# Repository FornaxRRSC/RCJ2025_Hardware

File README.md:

# Hardware

機体に搭載している基板のリポジトリです。  
それぞれの基板の解説は<https://fornax-rrsc.com>に掲載しています。

## 既知の欠陥

最新の基板の欠陥のみ記載
* MainBoard Rev.3のSTM32H723とSTM32F446間のUARTがTX,RX同士をつないでいる
* MainBoard Rev.3のオペアンプのフットプリントが間違っている

## License

**CERN-OHL-P v2**

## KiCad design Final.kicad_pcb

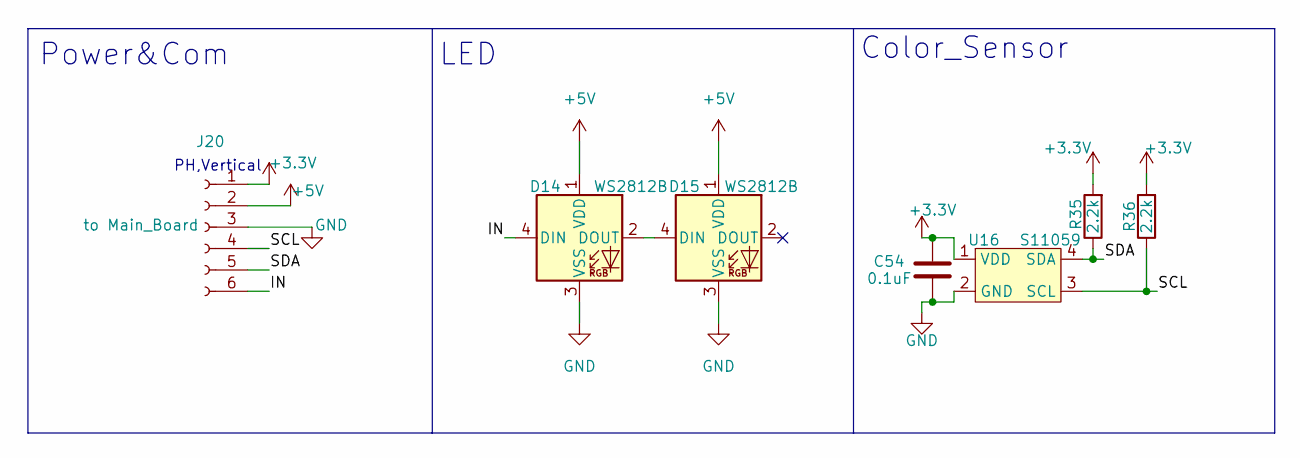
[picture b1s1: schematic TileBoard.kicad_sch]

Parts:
C54: 0.1uF; C_0603_1608Metric
D14, D15: WS2812B; LED_WS2812B_PLCC4_5.0x5.0mm_P3.2mm
J20: to Main_Board; PinHeader_1x06_P2.54mm_Vertical
R35, R36: 2.2k; R_0603_1608Metric
U16: S11059

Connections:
+3.3V: C54.1, J20.1, R35.2, R36.2, U16.1 (VDD); also elsewhere on the board
+5V: D14.1 (VDD), D15.1 (VDD), J20.2; also elsewhere on the board
/Tile_Board/IN: D14.4 (DIN), J20.6
/Tile_Board/SCL: J20.4, R36.1, U16.3 (SCL)
/Tile_Board/SDA: J20.5, R35.1, U16.4 (SDA)
GND: C54.2, D14.3 (VSS), D15.3 (VSS), J20.3, U16.2 (GND); also elsewhere on the board
unnamed: D14.2 (DOUT), D15.4 (DIN)

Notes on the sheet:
Color_Sensor
LED
Power&Com
PH,Vertical

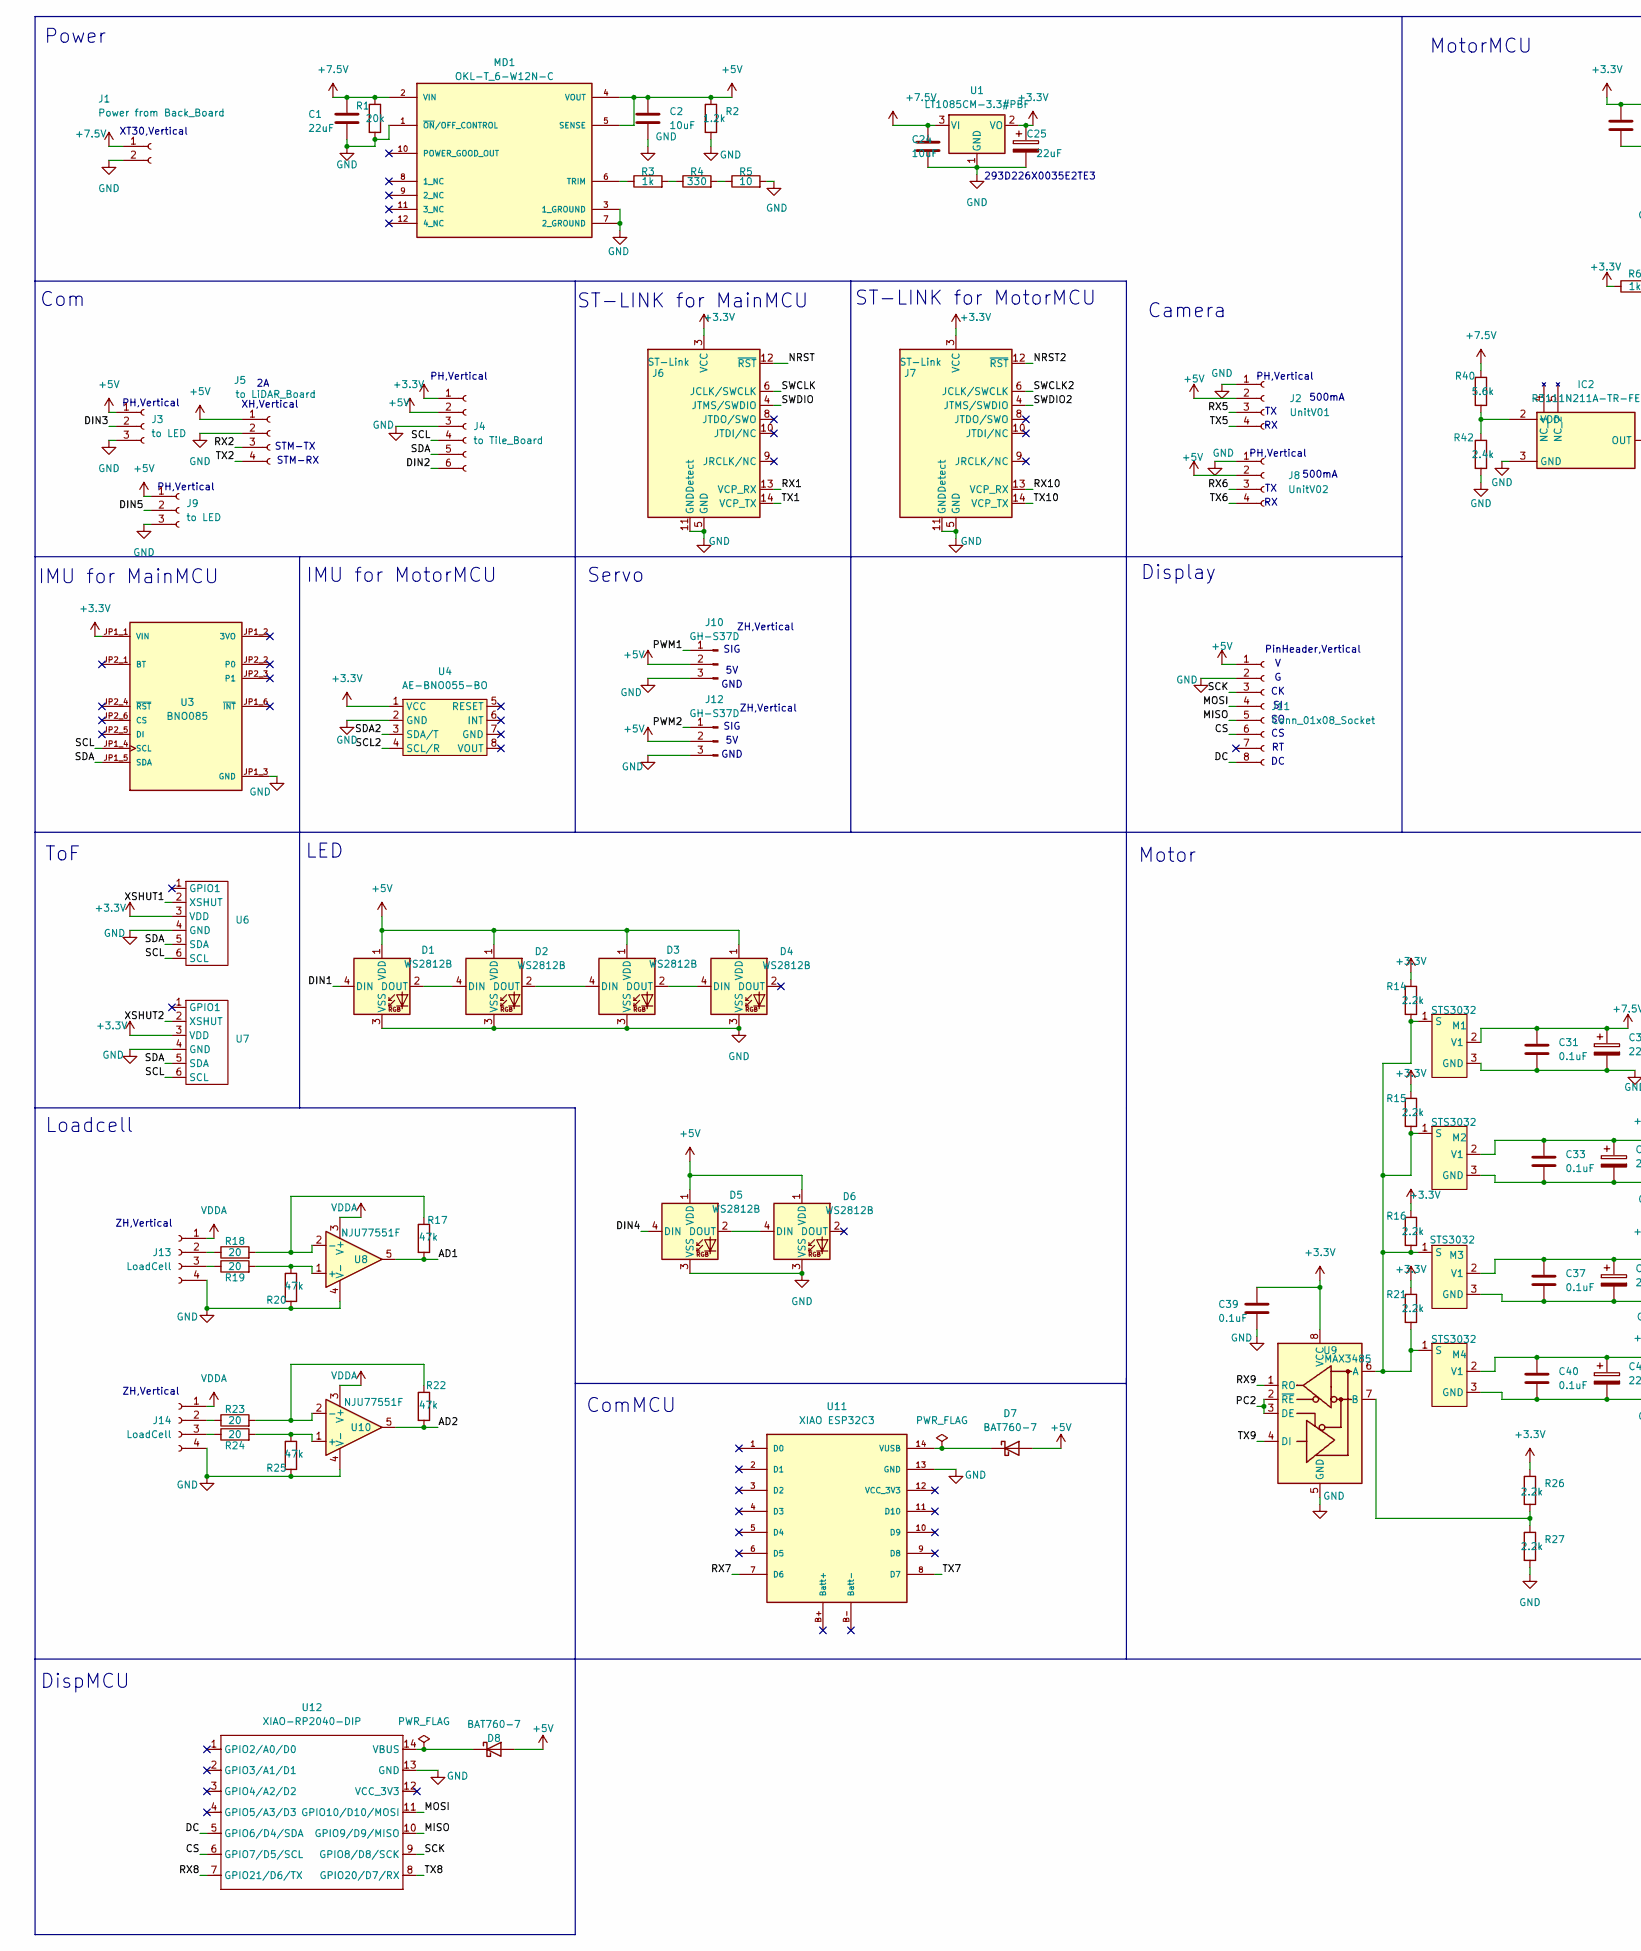
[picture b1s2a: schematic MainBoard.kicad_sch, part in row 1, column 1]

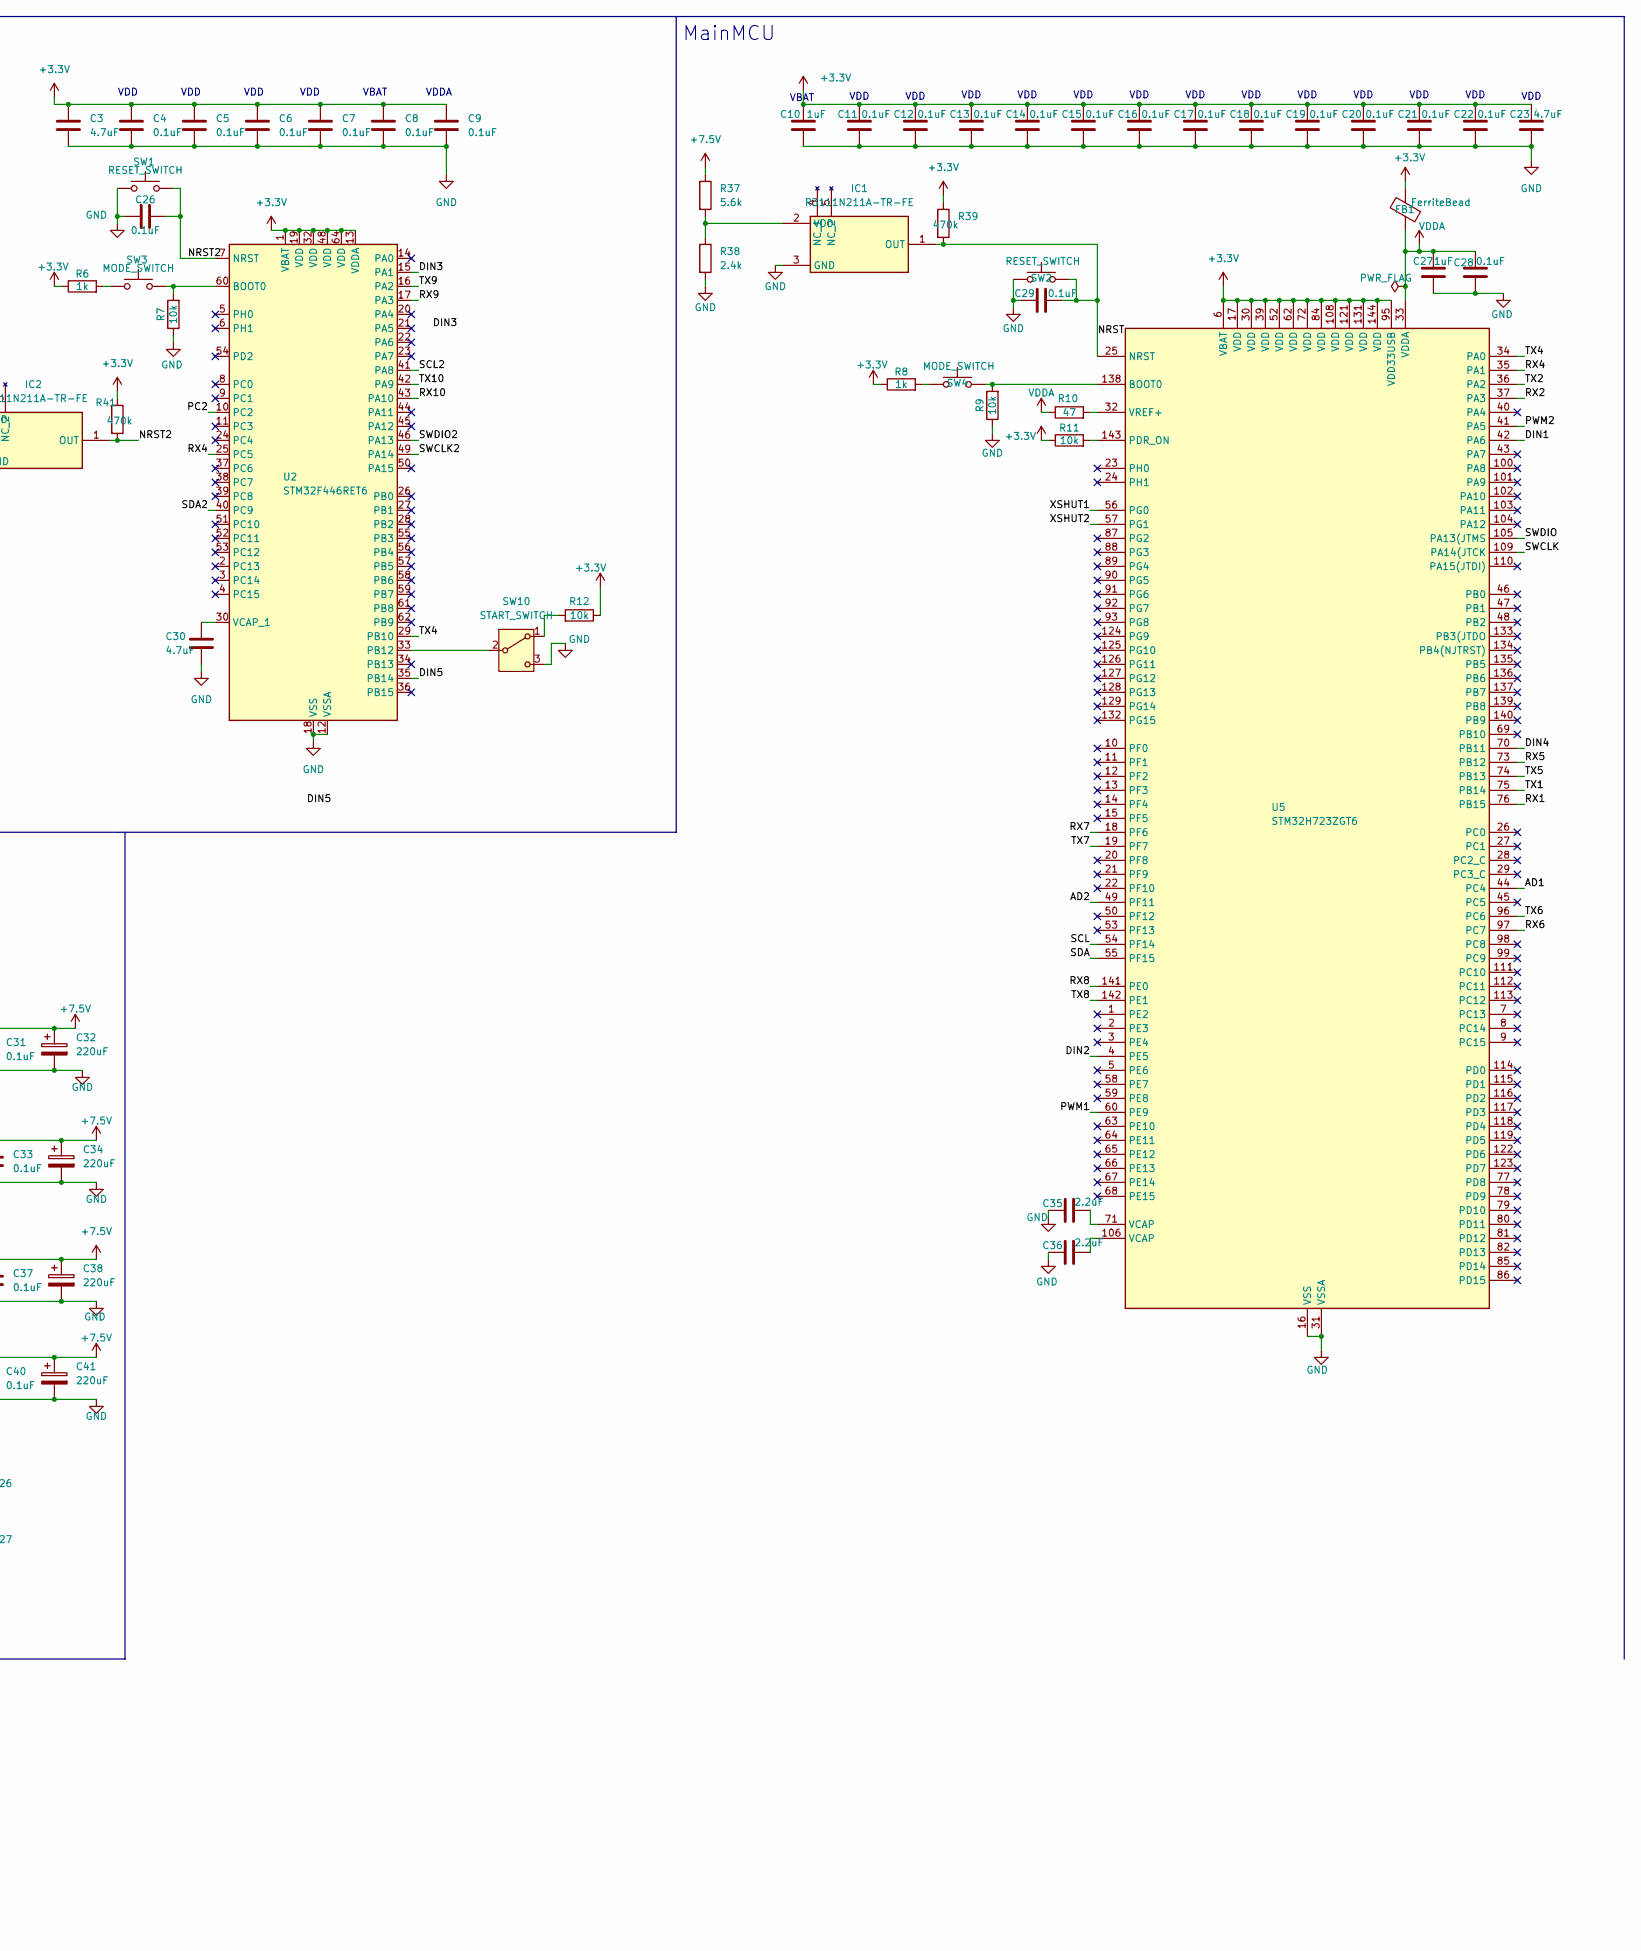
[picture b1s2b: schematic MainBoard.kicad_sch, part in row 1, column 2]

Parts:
C1: 22uF; C_0402_1005Metric
C2: 10uF; C_0402_1005Metric
C3, C23, C30: 4.7uF; C_0402_1005Metric
C4, C5, C6, C7, C8, C9, C11, C12, C13, C14, C15, C16, C17, C18, C19, C20, C21, C22, C28, C31, C33, C37, C39, C40: 0.1uF; C_0402_1005Metric
C10, C27: 1uF; C_0402_1005Metric
C24: 10uF; C_0603_1608Metric_Pad1.08x0.95mm_HandSolder
C25: 22uF; CP_EIA-7343-15_Kemet-W
C26, C29: 0.1uF; C_0603_1608Metric_Pad1.08x0.95mm_HandSolder
C32, C34, C38, C41: 220uF; CP_Elec_10x10
C35, C36: 2.2uF; C_0402_1005Metric
D1, D2, D3, D4, D5, D6: WS2812B; LED_WS2812B_PLCC4_5.0x5.0mm_P3.2mm
D7, D8: BAT760-7; D_SOD-323F
FB1: FerriteBead; L_0603_1608Metric
IC1, IC2: R3111N211A-TR-FE; SOT95P280X130-5N; Mouser Part Number 848-R3111N211A-TR-FE
J1: Power from Back_Board; AMASS_XT30U-M_1x02_P5.0mm_Vertical
J2: UnitV01; JST_PH_B4B-PH-K_1x04_P2.00mm_Vertical
J3, J9: to LED; JST_PH_B3B-PH-K_1x03_P2.00mm_Vertical
J4: to Tile_Board; PinSocket_1x06_P2.54mm_Vertical
J5: to LiDAR_Board; JST_XH_B4B-XH-A_1x04_P2.50mm_Vertical
J6, J7: ST-Link; CONN14_3220-14_CNC
J8: UnitV02; JST_PH_B4B-PH-K_1x04_P2.00mm_Vertical
J10, J12: GH-S37D; JST_ZH_B3B-ZR_1x03_P1.50mm_Vertical
J11: Conn_01x08_Socket; PinSocket_1x08_P2.54mm_Vertical
J13, J14: LoadCell; JST_ZH_B4B-ZR_1x04_P1.50mm_Vertical
M1, M2, M3, M4: STS3032; JST_XH_B3B-XH-A_1x03_P2.50mm_Vertical
MD1: OKL-T_6-W12N-C; MURATA_OKL-T-6-W12N-C_0; MOUSER_PART_NUMBER 580-OKL-T/6-W12N-C; MOUSER_DESCRIPTION Non-Isolated DC/DC Converters 12Vin .59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
R1: 20k; R_0402_1005Metric
R2: 1.2k; R_0402_1005Metric
R3: 1k; R_0402_1005Metric
R4: 330; R_0402_1005Metric
R5: 10; R_0402_1005Metric
R6, R8: 1k; R_0603_1608Metric_Pad0.98x0.95mm_HandSolder
R7, R9: 10k; R_0603_1608Metric_Pad0.98x0.95mm_HandSolder
R10: 47; R_0402_1005Metric
R11, R12: 10k; R_0402_1005Metric
R14, R15, R16, R21, R26, R27: 2.2k; R_0402_1005Metric
R17, R20, R22, R25: 47k; R_0402_1005Metric
R18, R19, R23, R24: 20; R_0402_1005Metric
R37, R40: 5.6k; R_0402_1005Metric
R38, R42: 2.4k; R_0402_1005Metric
R39, R41: 470k; R_0402_1005Metric
SW1, SW2: RESET_SWITCH; SW_SKRPACE010
SW3, SW4: MODE_SWITCH; SW_SKRPACE010
SW10: START_SWITCH; B12AP_NKK
U1: LT1085CM-3.3#PBF; TO-263-3_TabPin2
U2: STM32F446RET6; LQFP-64_10x10mm_P0.5mm
U3: BNO085; PARTREV 2021-03-16
U4: AE-BNO055-BO
U5: STM32H723ZGT6; LQFP-144_20x20mm_P0.5mm
U6, U7: PinSocket_1x06_P2.54mm_Vertical
U8, U10: NJU77551F; SOT-23-5
U9: MAX3485; SOIC-8_3.9x4.9mm_P1.27mm
U11: XIAO ESP32C3; XIAO-14P-DIP
U12: XIAO-RP2040-DIP; XIAO-14P-DIP

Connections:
+3.3V: C3.1, C4.1, C5.1, C6.1, C7.1, C8.1, C9.1, C10.1, C11.1, C12.1, C13.1, C14.1, C15.1, C16.1, C17.1, C18.1, C19.1, C20.1, C21.1, C22.1, C23.1, C25.1, C39.1, FB1.2, J4.1, J6.3 (VCC), J7.3 (VCC), R6.1, R8.1, R11.1, R12.1, R14.1, R15.1, R16.1, R21.1, R26.1, R39.1, R41.1, U1.2 (VO), U2.1 (VBAT), U2.13 (VDDA), U2.19 (VDD), U2.32 (VDD), U2.48 (VDD), U2.64 (VDD), U3.JP1_1 (VIN), U4.1 (VCC), U5.6 (VBAT), U5.17 (VDD), U5.30 (VDD), U5.39 (VDD), U5.52 (VDD), U5.62 (VDD), U5.72 (VDD), U5.84 (VDD), U5.95 (VDD33USB), U5.108 (VDD), U5.121 (VDD), U5.131 (VDD), U5.144 (VDD), U6.3 (VDD), U7.3 (VDD), U9.8 (VCC); also elsewhere on the board
+5V: C2.1, D1.1 (VDD), D2.1 (VDD), D3.1 (VDD), D4.1 (VDD), D5.1 (VDD), D6.1 (VDD), D7.2 (A), D8.2 (A), J2.2, J3.1, J4.2, J5.1, J8.2, J9.1, J10.2, J11.1, J12.2, MD1.4 (VOUT), MD1.5 (SENSE), R2.1; also elsewhere on the board
+7.5V: C1.1, C24.1, C31.1, C32.1, C33.1, C34.1, C37.1, C38.1, C40.1, C41.1, J1.1, M1.2 (V1), M2.2 (V1), M3.2 (V1), M4.2 (V1), MD1.2 (VIN), R1.1, R37.1, R40.1, U1.3 (VI); also elsewhere on the board
/Main_Board/AD1: R17.2, U5.44 (PC4), U8.5
/Main_Board/AD2: R22.2, U5.49 (PF11), U10.5
/Main_Board/CS: J11.6, U12.6 (GPIO7/D5/SCL)
/Main_Board/DC: J11.8, U12.5 (GPIO6/D4/SDA)
/Main_Board/DIN1: D1.4 (DIN), U5.42 (PA6)
/Main_Board/DIN2: J4.6, U5.4 (PE5)
/Main_Board/DIN3: J3.2, U2.15 (PA1)
/Main_Board/DIN4: D5.4 (DIN), U5.70 (PB11)
/Main_Board/DIN5: J9.2, U2.35 (PB14)
/Main_Board/MISO: J11.5, U12.10 (GPIO9/D9/MISO)
/Main_Board/MOSI: J11.4, U12.11 (GPIO10/D10/MOSI)
/Main_Board/NRST: C29.2, IC1.1 (OUT), J6.12 (~RST), R39.2, SW2.2, U5.25 (NRST)
/Main_Board/NRST2: C26.2, IC2.1 (OUT), J7.12 (~RST), R41.2, SW1.2, U2.7 (NRST)
/Main_Board/PC2: U2.10 (PC2), U9.2 (~RE), U9.3 (DE)
/Main_Board/PWM1: J10.1, U5.60 (PE9)
/Main_Board/PWM2: J12.1, U5.41 (PA5)
/Main_Board/RX1: J6.13 (VCP_RX), U5.76 (PB15)
/Main_Board/RX2: J5.3, U5.37 (PA3)
/Main_Board/RX4: U2.25 (PC5), U5.35 (PA1)
/Main_Board/RX5: J2.3, U5.73 (PB12)
/Main_Board/RX6: J8.3, U5.97 (PC7)
/Main_Board/RX7: U5.18 (PF6), U11.7 (D6)
/Main_Board/RX8: U5.141 (PE0), U12.7 (GPIO21/D6/TX)
/Main_Board/RX9: U2.17 (PA3), U9.1 (RO)
/Main_Board/RX10: J7.13 (VCP_RX), U2.43 (PA10)
/Main_Board/SCK: J11.3, U12.9 (GPIO8/D8/SCK)
/Main_Board/SCL: J4.4, U3.JP1_4 (SCL), U5.54 (PF14), U6.6 (SCL), U7.6 (SCL)
/Main_Board/SCL2: U2.41 (PA8), U4.4 (SCL/R)
/Main_Board/SDA: J4.5, U3.JP1_5 (SDA), U5.55 (PF15), U6.5 (SDA), U7.5 (SDA)
/Main_Board/SDA2: U2.40 (PC9), U4.3 (SDA/T)
/Main_Board/SWCLK: J6.6 (JCLK/SWCLK), U5.109 (PA14(JTCK)
/Main_Board/SWCLK2: J7.6 (JCLK/SWCLK), U2.49 (PA14)
/Main_Board/SWDIO: J6.4 (JTMS/SWDIO), U5.105 (PA13(JTMS)
/Main_Board/SWDIO2: J7.4 (JTMS/SWDIO), U2.46 (PA13)
/Main_Board/TX1: J6.14 (VCP_TX), U5.75 (PB14)
/Main_Board/TX2: J5.4, U5.36 (PA2)
/Main_Board/TX4: U2.29 (PB10), U5.34 (PA0)
/Main_Board/TX5: J2.4, U5.74 (PB13)
/Main_Board/TX6: J8.4, U5.96 (PC6)
/Main_Board/TX7: U5.19 (PF7), U11.8 (D7)
/Main_Board/TX8: U5.142 (PE1), U12.8 (GPIO20/D7/RX)
/Main_Board/TX9: U2.16 (PA2), U9.4 (DI)
/Main_Board/TX10: J7.14 (VCP_TX), U2.42 (PA9)
/Main_Board/XSHUT1: U5.56 (PG0), U6.2 (XSHUT)
/Main_Board/XSHUT2: U5.57 (PG1), U7.2 (XSHUT)
GND: C1.2, C2.2, C3.2, C4.2, C5.2, C6.2, C7.2, C8.2, C9.2, C10.2, C11.2, C12.2, C13.2, C14.2, C15.2, C16.2, C17.2, C18.2, C19.2, C20.2, C21.2, C22.2, C23.2, C24.2, C25.2, C26.1, C27.2, C28.2, C29.1, C30.2, C31.2, C32.2, C33.2, C34.2, C35.1, C36.1, C37.2, C38.2, C39.2, C40.2, C41.2, D1.3 (VSS), D2.3 (VSS), D3.3 (VSS), D4.3 (VSS), D5.3 (VSS), D6.3 (VSS), IC1.3 (GND), IC2.3 (GND), J1.2, J2.1, J3.3, J4.3, J5.2, J6.5 (GND), J6.7 (GND), J6.11 (GNDDetect), J7.5 (GND), J7.7 (GND), J7.11 (GNDDetect), J8.1, J9.3, J10.3, J11.2, J12.3, J13.4, J14.4, M1.3 (GND), M2.3 (GND), M3.3 (GND), M4.3 (GND), MD1.1 (~ON/OFF_CONTROL), MD1.3 (1_GROUND), MD1.7 (2_GROUND), R1.2, R2.2, R5.2, R7.1, R9.1, R20.2, R25.2, R27.2, R38.2, R42.2, SW1.1, SW2.1, SW10.3 (C), U1.1 (GND), U2.12 (VSSA), U2.18 (VSS), U2.31 (VSS), U2.47 (VSS), U2.63 (VSS), U3.JP1_3 (GND), U4.2 (GND), U5.16 (VSS), U5.31 (VSSA), U5.38 (VSS), U5.51 (VSS), U5.61 (VSS), U5.83 (VSS), U5.94 (VSS), U5.107 (VSS), U5.120 (VSS), U5.130 (VSS), U6.4 (GND), U7.4 (GND), U8.4 (V-), U9.5 (GND), U10.4 (V-), U11.13 (GND), U12.13 (GND); also elsewhere on the board
unnamed: C35.2, U5.71 (VCAP)
unnamed: C36.2, U5.106 (VCAP)
unnamed: D1.2 (DOUT), D2.4 (DIN)
unnamed: D2.2 (DOUT), D3.4 (DIN)
unnamed: D3.2 (DOUT), D4.4 (DIN)
unnamed: D5.2 (DOUT), D6.4 (DIN)
unnamed: D7.1 (K), U11.14 (VUSB)
unnamed: D8.1 (K), U12.14 (VBUS)
unnamed: IC1.2 (VDD), R37.2, R38.1
unnamed: IC2.2 (VDD), R40.2, R42.1
unnamed: J13.2, R18.1
unnamed: J13.3, R19.1
unnamed: J14.2, R23.1
unnamed: J14.3, R24.1
unnamed: M1.1 (S), M2.1 (S), M3.1 (S), M4.1 (S), R14.2, R15.2, R16.2, R21.2, U9.6 (A)
unnamed: MD1.6 (TRIM), R3.1
unnamed: R3.2, R4.1
unnamed: R4.2, R5.1
unnamed: R6.2, SW3.1
unnamed: R8.2, SW4.1
unnamed: R12.2, SW10.1 (A)
unnamed: SW10.2 (B), U2.33 (PB12)
unnamed: R7.2, SW3.2, U2.60 (BOOT0)
unnamed: C30.1, U2.30 (VCAP_1)
unnamed: R9.2, SW4.2, U5.138 (BOOT0)
unnamed: R11.2, U5.143 (PDR_ON)
unnamed: R10.2, U5.32 (VREF+)
unnamed: R19.2, R20.1, U8.1 (+)
unnamed: R17.1, R18.2, U8.2 (-)
unnamed: R26.2, R27.1, U9.7 (B)
unnamed: R24.2, R25.1, U10.1 (+)
unnamed: R22.1, R23.2, U10.2 (-)
VDDA: C27.1, C28.1, FB1.1, J13.1, J14.1, R10.1, U5.33 (VDDA), U8.3 (V+), U10.3 (V+)

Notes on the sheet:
VDD
MainMCU
LED
293D226X0035E2TE3
PH,Vertical
GND
VBAT
Servo
500mA
ZH,Vertical
STM-TX
XT30,Vertical
SIG
MotorMCU
ST-LINK for MainMCU
Loadcell
DispMCU
Motor
PinHeader,Vertical
ComMCU
STM-RX
IMU for MainMCU
ST-LINK for MotorMCU
Display
XH,Vertical
Camera
ToF
Power
IMU for MotorMCU
VDDA
Com

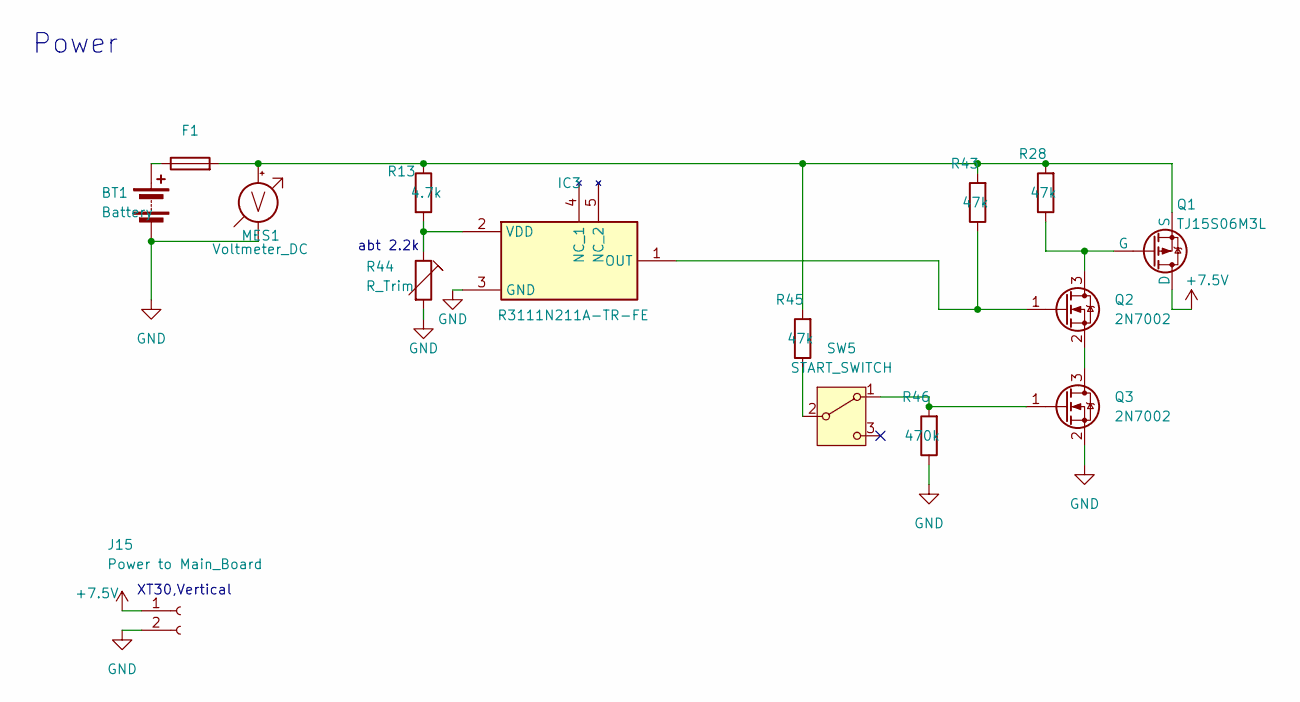
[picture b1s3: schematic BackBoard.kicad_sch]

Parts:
BT1: Battery; AMASS_XT30U-M_1x02_P5.0mm_Vertical
F1: 0451015.MRL; 0451Series_LTF
IC3: R3111N211A-TR-FE; SOT95P280X130-5N; Mouser Part Number 848-R3111N211A-TR-FE
J15: Power to Main_Board; AMASS_XT30U-M_1x02_P5.0mm_Vertical
MES1: Voltmeter_DC; JST_PH_B2B-PH-K_1x02_P2.00mm_Vertical
Q1: TJ15S06M3L; TO-252-2
Q2, Q3: 2N7002; SOT-23
R13: 4.7k; R_0603_1608Metric_Pad0.98x0.95mm_HandSolder
R28, R43, R45: 47k; R_0603_1608Metric_Pad0.98x0.95mm_HandSolder
R44: R_Trim; TRIM_3362P-1-103LF
R46: 470k; R_0603_1608Metric_Pad0.98x0.95mm_HandSolder
SW5: START_SWITCH; B12AP_NKK

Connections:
+7.5V: J15.1, Q1.1 (D); also elsewhere on the board
GND: BT1.2 (-), IC3.3 (GND), J15.2, MES1.1 (-), Q3.2 (S), R44.2, R46.1; also elsewhere on the board
unnamed: BT1.1 (+), F1.1
unnamed: IC3.1 (OUT), Q2.1 (G), R43.1
unnamed: IC3.2 (VDD), R13.2, R44.1
unnamed: F1.2, MES1.2 (+), Q1.3 (S), R13.1, R28.2, R43.2, R45.2
unnamed: Q1.2 (G), Q2.3 (D), R28.1
unnamed: Q2.2 (S), Q3.3 (D)
unnamed: Q3.1 (G), R46.2, SW5.1 (A)
unnamed: R45.1, SW5.2 (B)

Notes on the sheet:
Power
abt 2.2k
XT30,Vertical

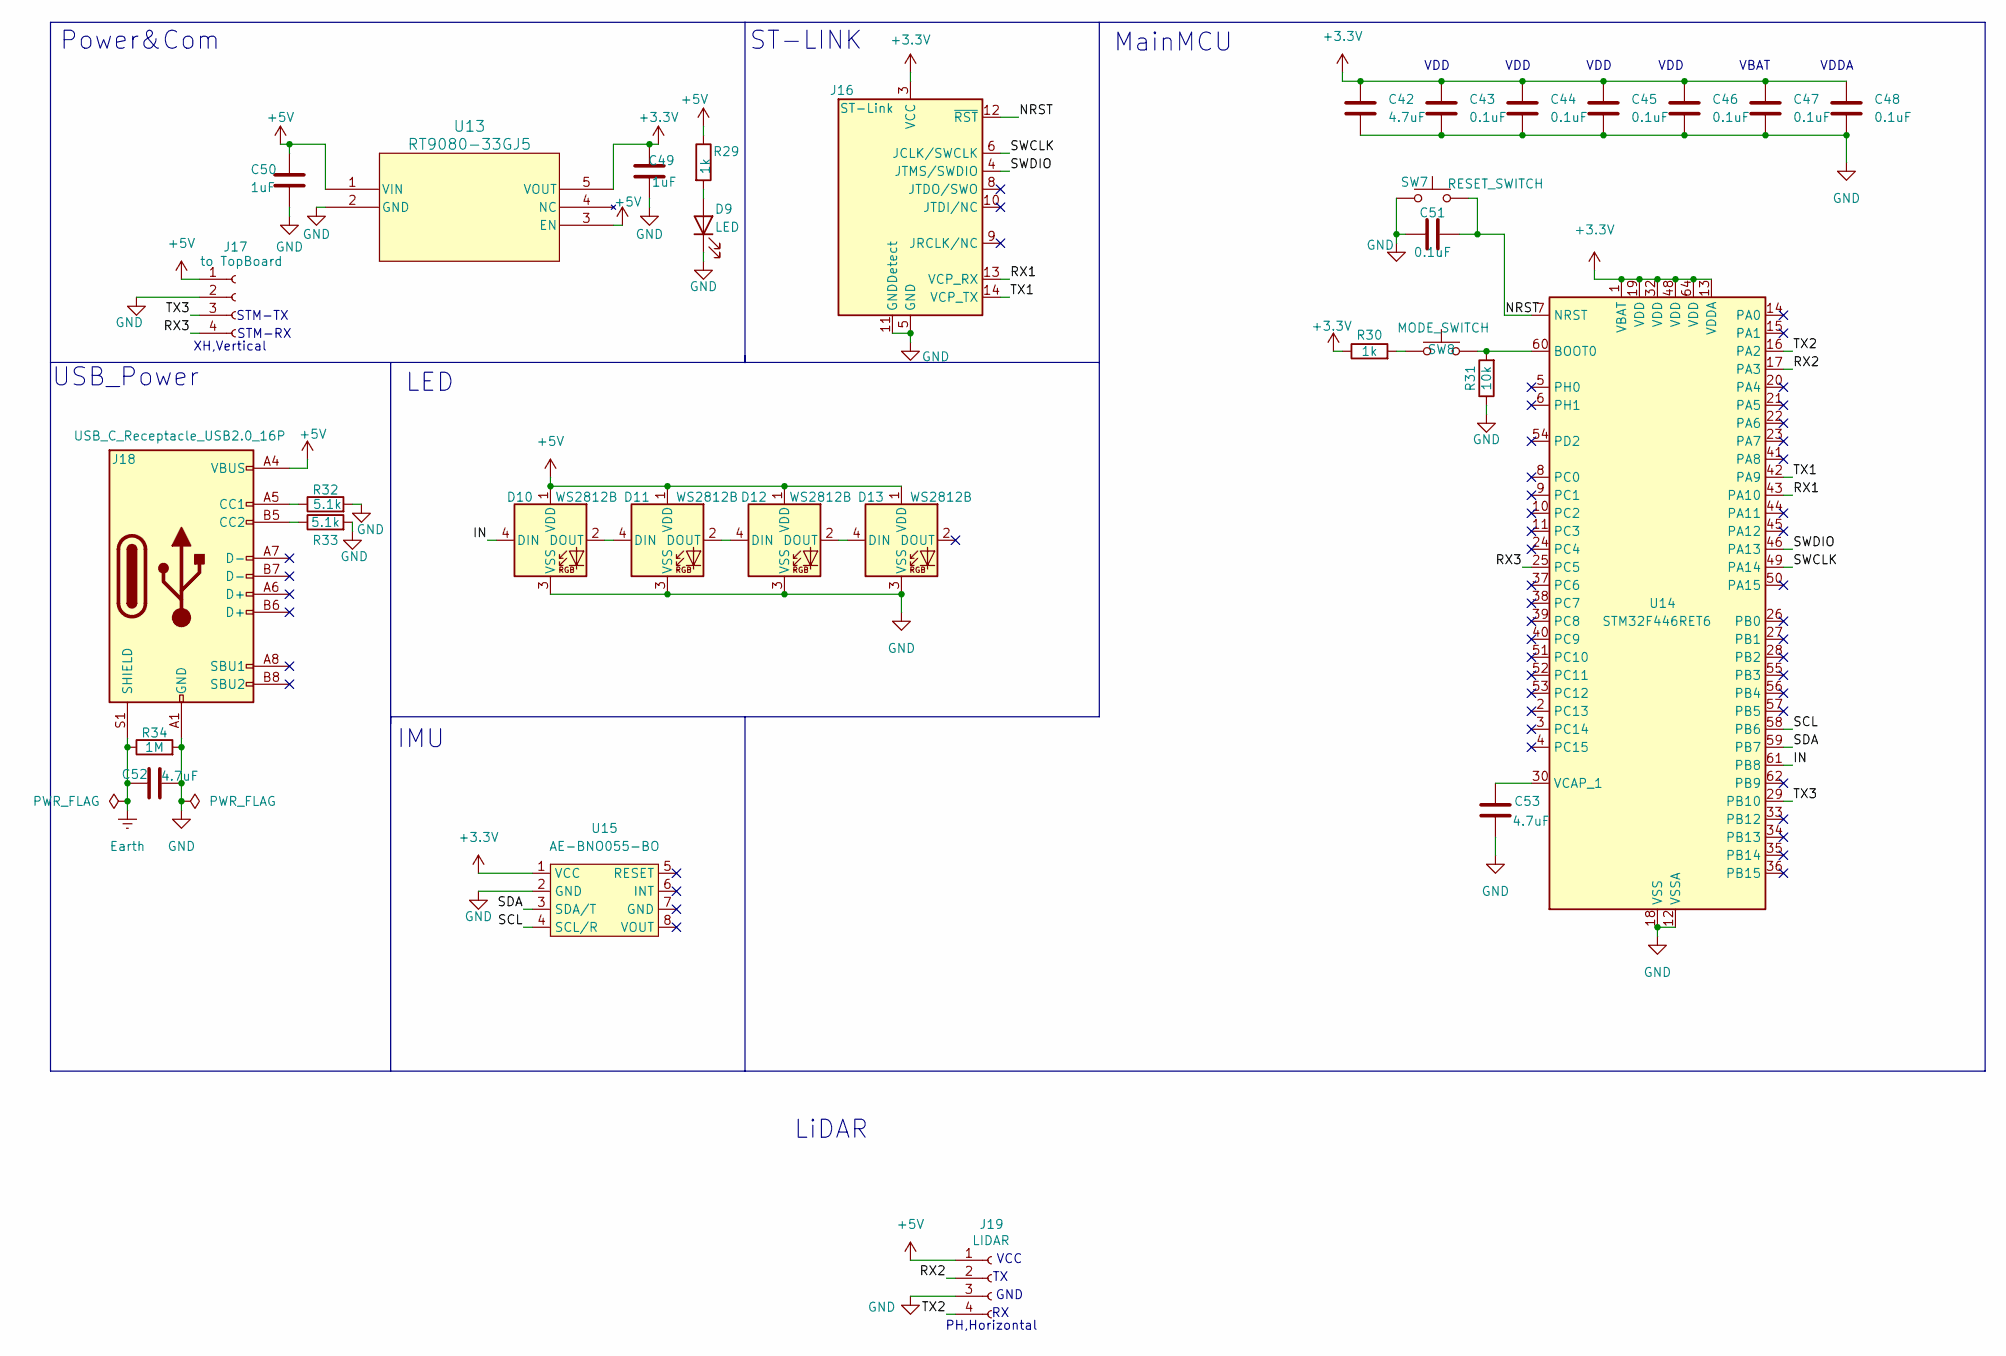
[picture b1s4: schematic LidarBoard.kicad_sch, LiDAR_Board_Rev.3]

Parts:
C42, C52, C53: 4.7uF; C_0603_1608Metric
C43, C44, C45, C46, C47, C48: 0.1uF; C_0603_1608Metric
C49, C50: 1uF; C_0603_1608Metric
C51: 0.1uF; C_0603_1608Metric_Pad1.08x0.95mm_HandSolder
D9: LED; LED_0603_1608Metric
D10, D11, D12, D13: WS2812B; LED_WS2812B_PLCC4_5.0x5.0mm_P3.2mm
J16: ST-Link; CONN14_3220-14_CNC
J17: to TopBoard; JST_XH_B4B-XH-A_1x04_P2.50mm_Vertical
J18: USB_C_Receptacle_USB2.0_16P; USB_C_Receptacle_G-Switch_GT-USB-7010ASV
J19: LIDAR; JST_PH_S4B-PH-K_1x04_P2.00mm_Horizontal
R29: 1k; R_0603_1608Metric
R30: 1k; R_0603_1608Metric_Pad0.98x0.95mm_HandSolder
R31: 10k; R_0603_1608Metric_Pad0.98x0.95mm_HandSolder
R32, R33: 5.1k; R_0603_1608Metric
R34: 1M; R_0603_1608Metric
SW7: RESET_SWITCH; SW_SKRPACE010
SW8: MODE_SWITCH; SW_SKRPACE010
U13: RT9080-33GJ5; TSOT-23-5
U14: STM32F446RET6; LQFP-64_10x10mm_P0.5mm
U15: AE-BNO055-BO

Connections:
+3.3V: C42.1, C43.1, C44.1, C45.1, C46.1, C47.1, C48.1, C49.1, J16.3 (VCC), R30.1, U13.5 (VOUT), U14.1 (VBAT), U14.13 (VDDA), U14.19 (VDD), U14.32 (VDD), U14.48 (VDD), U14.64 (VDD), U15.1 (VCC); also elsewhere on the board
+5V: C50.1, D10.1 (VDD), D11.1 (VDD), D12.1 (VDD), D13.1 (VDD), J17.1, J18.A4 (VBUS), J18.A9 (VBUS), J18.B4 (VBUS), J18.B9 (VBUS), J19.1, R29.1, U13.1 (VIN), U13.3 (EN); also elsewhere on the board
/LiDAR_Board/IN: D10.4 (DIN), U14.61 (PB8)
/LiDAR_Board/NRST: C51.2, J16.12 (~RST), SW7.2, U14.7 (NRST)
/LiDAR_Board/RX1: J16.13 (VCP_RX), U14.43 (PA10)
/LiDAR_Board/RX2: J19.2, U14.17 (PA3)
/LiDAR_Board/RX3: J17.4, U14.25 (PC5)
/LiDAR_Board/SCL: U14.58 (PB6), U15.4 (SCL/R)
/LiDAR_Board/SDA: U14.59 (PB7), U15.3 (SDA/T)
/LiDAR_Board/SWCLK: J16.6 (JCLK/SWCLK), U14.49 (PA14)
/LiDAR_Board/SWDIO: J16.4 (JTMS/SWDIO), U14.46 (PA13)
/LiDAR_Board/TX1: J16.14 (VCP_TX), U14.42 (PA9)
/LiDAR_Board/TX2: J19.4, U14.16 (PA2)
/LiDAR_Board/TX3: J17.3, U14.29 (PB10)
Earth: C52.1, J18.S1 (SHIELD), R34.1
GND: C42.2, C43.2, C44.2, C45.2, C46.2, C47.2, C48.2, C49.2, C50.2, C51.1, C52.2, C53.2, D9.1 (K), D10.3 (VSS), D11.3 (VSS), D12.3 (VSS), D13.3 (VSS), J16.5 (GND), J16.7 (GND), J16.11 (GNDDetect), J17.2, J18.A1 (GND), J18.A12 (GND), J18.B1 (GND), J18.B12 (GND), J19.3, R31.1, R32.2, R33.2, R34.2, SW7.1, U13.2 (GND), U14.12 (VSSA), U14.18 (VSS), U14.31 (VSS), U14.47 (VSS), U14.63 (VSS), U15.2 (GND); also elsewhere on the board
unnamed: D9.2 (A), R29.2
unnamed: D10.2 (DOUT), D11.4 (DIN)
unnamed: D11.2 (DOUT), D12.4 (DIN)
unnamed: D12.2 (DOUT), D13.4 (DIN)
unnamed: J18.A5 (CC1), R32.1
unnamed: J18.B5 (CC2), R33.1
unnamed: R30.2, SW8.1
unnamed: R31.2, SW8.2, U14.60 (BOOT0)
unnamed: C53.1, U14.30 (VCAP_1)

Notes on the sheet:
STM-TX
VDD
VCC
MainMCU
VDDA
STM-RX
PH,Horizontal
IMU
LiDAR
LED
GND
VBAT
USB_Power
Power&Com
XH,Vertical
ST-LINK

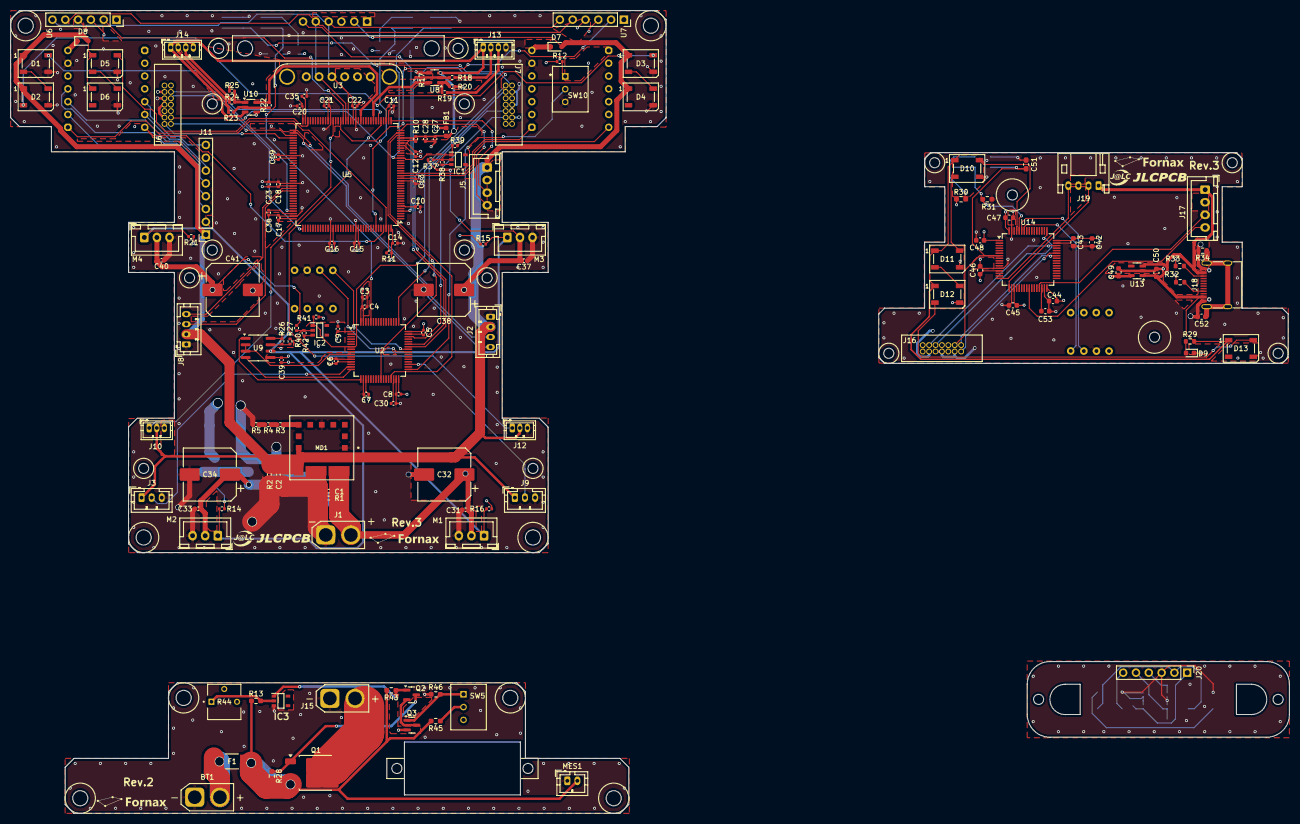
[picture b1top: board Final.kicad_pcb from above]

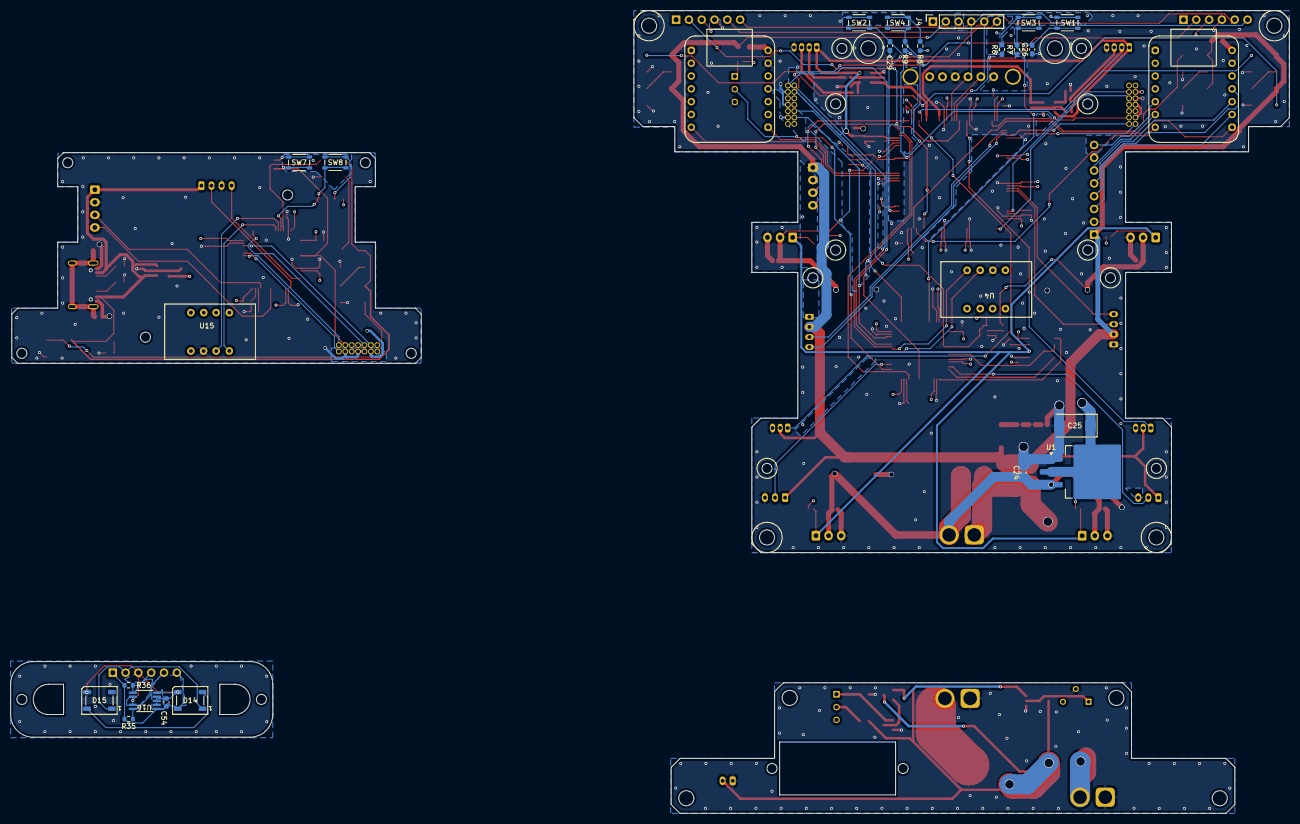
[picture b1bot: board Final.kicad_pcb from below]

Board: 4 copper layers, 253.6 x 159.2 mm, 174 parts (26 on the bottom side), 116 nets.

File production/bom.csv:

Designator,Footprint,Quantity,Value,LCSC Part #
C1,0402,1,22uF,
"C10, C27",0402,2,1uF,
"C11, C12, C13, C14, C15, C16, C17, C18, C19, C20, C21, C22, C28, C31, C33, C37, C39, C4, C40, C5, C6, C7, C8, C9",0402,24,0.1uF,
C2,0402,1,10uF,
"C23, C3, C30",0402,3,4.7uF,
C24,0603,1,10uF,
C25,CP_EIA-7343-15_Kemet-W,1,22uF,
"C26, C29",0603,2,0.1uF,
"C32, C34, C38, C41",CP_Elec_10x10,4,220uF,
"C35, C36",0402,2,2.2uF,
"D1, D2, D3, D4, D5, D6",LED_WS2812B_PLCC4_5.0x5.0mm_P3.2mm,6,WS2812B,
"D7, D8",D_SOD-323F,2,BAT760-7,
FB1,0603,1,FerriteBead,
"IC1, IC2",SOT95P280X130-5N,2,R3111N211A-TR-FE,
J1,AMASS_XT30U-M_1x02_P5.0mm_Vertical,1,Power from Back_Board,
"J10, J12",JST_ZH_B3B-ZR_1x03_P1.50mm_Vertical,2,GH-S37D,
J11,PinSocket_1x08_P2.54mm_Vertical,1,Conn_01x08_Socket,
"J13, J14",JST_ZH_B4B-ZR_1x04_P1.50mm_Vertical,2,LoadCell,
J2,JST_PH_B4B-PH-K_1x04_P2.00mm_Vertical,1,UnitV01,
"J3, J9",JST_PH_B3B-PH-K_1x03_P2.00mm_Vertical,2,to LED,
J4,PinSocket_1x06_P2.54mm_Vertical,1,to Tile_Board,
J5,JST_XH_B4B-XH-A_1x04_P2.50mm_Vertical,1,to LiDAR_Board,
"J6, J7",CONN14_3220-14_CNC,2,ST-Link,
J8,JST_PH_B4B-PH-K_1x04_P2.00mm_Vertical,1,UnitV02,
"M1, M2, M3, M4",JST_XH_B3B-XH-A_1x03_P2.50mm_Vertical,4,STS3032,
MD1,MURATA_OKL-T-6-W12N-C_0,1,OKL-T_6-W12N-C,OKL-T/6-W12N-C
R1,0402,1,20k,
R10,0402,1,47,
"R11, R12",0402,2,10k,
"R14, R15, R16, R21, R26, R27",0402,6,2.2k,
"R17, R20, R22, R25",0402,4,47k,
"R18, R19, R23, R24",0402,4,20,
R2,0402,1,1.2k,
R3,0402,1,1k,
"R37, R40",0402,2,5.6k,
"R38, R42",0402,2,2.4k,
"R39, R41",0402,2,470k,
R4,0402,1,330,
R5,0402,1,10,
"R6, R8",0603,2,1k,
"R7, R9",0603,2,10k,
"SW1, SW2",SW_SKRPACE010,2,RESET_SWITCH,
SW10,B12AP_NKK,1,START_SWITCH,
"SW3, SW4",SW_SKRPACE010,2,MODE_SWITCH,
U1,TO-263-3_TabPin2,1,LT1085CM-3.3#PBF,
"U10, U8",SOT-23-5,2,NJU77551F,
U11,XIAO-14P-DIP,1,XIAO ESP32C3,
U12,XIAO-14P-DIP,1,XIAO-RP2040-DIP,
U2,LQFP-64_10x10mm_P0.5mm,1,STM32F446RET6,
U3,BNO085,1,BNO085,
U4,AE-BNO055-BO,1,AE-BNO055-BO,
U5,LQFP-144_20x20mm_P0.5mm,1,STM32H723ZGT6,
"U6, U7",PinSocket_1x06_P2.54mm_Vertical,2,~,
U9,SOIC-8_3.9x4.9mm_P1.27mm,1,MAX3485,
